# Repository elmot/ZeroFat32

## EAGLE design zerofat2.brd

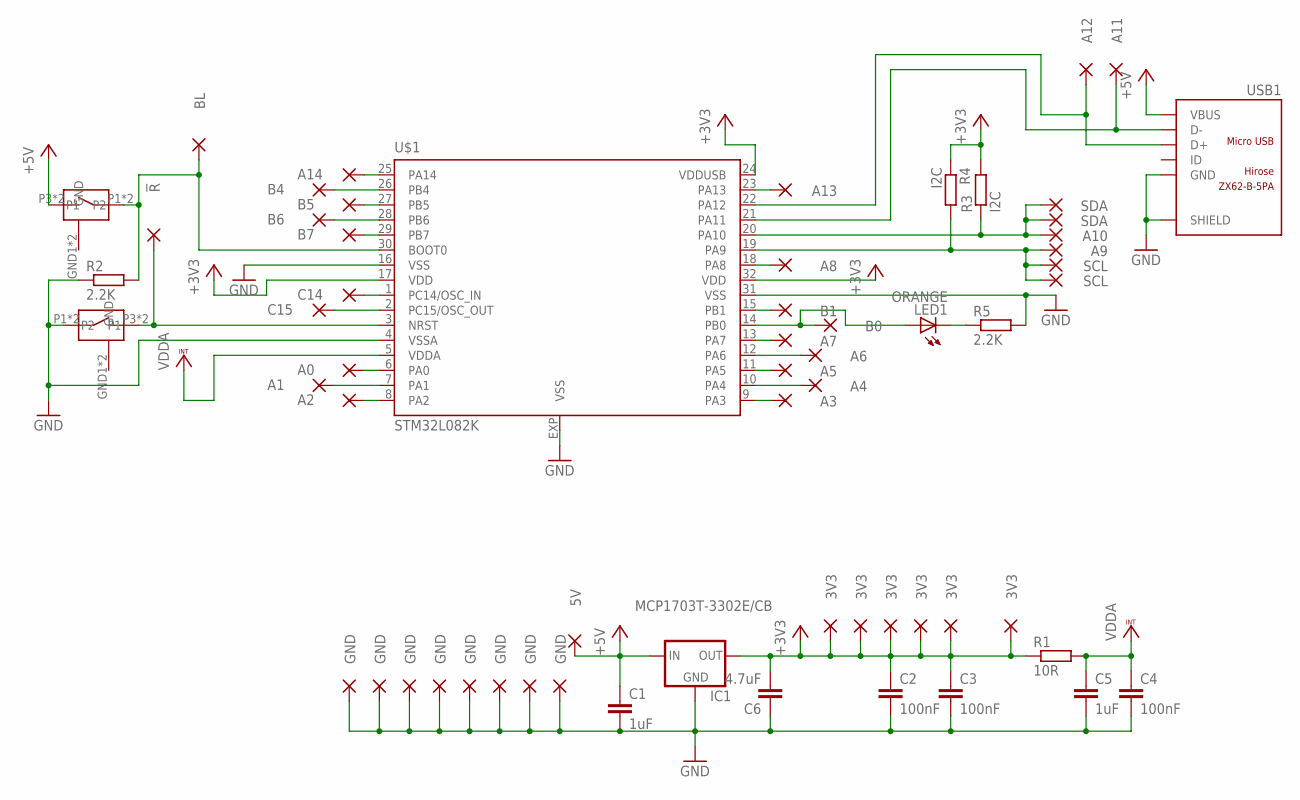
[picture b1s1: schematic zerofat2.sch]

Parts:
B: EVQPT5A15
C1, C5: 1uF; C0603
C2, C3, C4: 100nF; C0603
C6: 4.7uF; C0603
IC1: MCP1703T-3302E/CB; SOT23
LED1: ORANGE; CHIP-LED0603
PAD1, PAD20: SCL; PAD_MINIMAL
PAD2, PAD19: SDA; PAD_MINIMAL
PAD3: C14; PAD_MINIMAL
PAD4: C15; PAD_MINIMAL
PAD5, PAD22, PAD39, PAD43, PAD48, PAD49, PAD50, PAD51: GND; PAD_MINIMAL
PAD6: !R; PAD_MINIMAL
PAD7, PAD15, PAD21, PAD52, PAD53, PAD54: 3V3; PAD_MINIMAL
PAD8: A0; PAD_MINIMAL
PAD9: A2; PAD_MINIMAL
PAD10: A1; PAD_MINIMAL
PAD11: A3; PAD_MINIMAL
PAD12: A5; PAD_MINIMAL
PAD13: A7; PAD_MINIMAL
PAD14: B1; PAD_MINIMAL
PAD16: A4; PAD_MINIMAL
PAD17: A6; PAD_MINIMAL
PAD18: B0; PAD_MINIMAL
PAD24: A8; PAD_MINIMAL
PAD25: A9; PAD_MINIMAL
PAD26: A10; PAD_MINIMAL
PAD27: A13; PAD_MINIMAL
PAD29: A12; PAD_MINIMAL
PAD30: A11; PAD_MINIMAL
PAD31: A14; PAD_MINIMAL
PAD33: B5; PAD_MINIMAL
PAD34: B7; PAD_MINIMAL
PAD35: BL; PAD_MINIMAL
PAD36: B6; PAD_MINIMAL
PAD37: B4; PAD_MINIMAL
PAD45: 5V; PAD_MINIMAL
R: EVQPT5A15
R1: 10R; R0603
R2, R5: 2.2K; R0603
R3, R4: I2C; R0603
U$1: STM32L082K; UFQFPN32
USB1: ZX62-B-5PA; MICRO-USB5+6P-SMD-0.65-AB

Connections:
+3V3: C2.1, C3.1, C6.2, IC1.2 (OUT), PAD7.1, PAD15.1, PAD21.1, PAD52.1, PAD53.1, PAD54.1, R1.1, R3.2, R4.1, U$1.17 (VDD), U$1.24 (VDDUSB), U$1.32 (VDD)
+5V: B.P3 (P2), B.P4 (P2), C1.1, IC1.3 (IN), PAD45.1, USB1.1 (VBUS)
BOOT0: B.P1, B.P2 (P1), PAD35.1, R2.2, U$1.30 (BOOT0)
GND: C1.2, C2.2, C3.2, C4.2, C5.2, C6.1, IC1.1 (GND), PAD5.1, PAD22.1, PAD39.1, PAD43.1, PAD48.1, PAD49.1, PAD50.1, PAD51.1, R.P1, R.P2 (P1), R2.1, R5.2, U$1.4 (VSSA), U$1.16 (VSS), U$1.31 (VSS), U$1.EXP (VSS), USB1.5 (GND), USB1.P1 (SHIELD), USB1.P2 (SHIELD), USB1.P3 (SHIELD), USB1.P4 (SHIELD), USB1.P5 (SHIELD), USB1.P6 (SHIELD)
unnamed: PAD30.1, U$1.21 (PA11), USB1.2 (D-)
unnamed: LED1.A, PAD18.1, U$1.14 (PB0)
unnamed: PAD27.1, U$1.23 (PA13)
unnamed: PAD29.1, U$1.22 (PA12), USB1.3 (D+)
unnamed: PAD31.1, U$1.25 (PA14)
unnamed: PAD3.1, U$1.1 (PC14/OSC_IN)
unnamed: PAD37.1, U$1.26 (PB4)
unnamed: PAD33.1, U$1.27 (PB5)
unnamed: PAD36.1, U$1.28 (PB6)
unnamed: PAD4.1, U$1.2 (PC15/OSC_OUT)
unnamed: PAD8.1, U$1.6 (PA0)
unnamed: PAD10.1, U$1.7 (PA1)
unnamed: PAD9.1, U$1.8 (PA2)
unnamed: PAD11.1, U$1.9 (PA3)
unnamed: PAD16.1, U$1.10 (PA4)
unnamed: PAD12.1, U$1.11 (PA5)
unnamed: PAD17.1, U$1.12 (PA6)
unnamed: PAD13.1, U$1.13 (PA7)
unnamed: PAD24.1, U$1.18 (PA8)
unnamed: PAD14.1, U$1.15 (PB1)
unnamed: PAD1.1, PAD20.1, PAD25.1, R4.2, U$1.19 (PA9)
unnamed: PAD34.1, U$1.29 (PB7)
unnamed: PAD2.1, PAD19.1, PAD26.1, R3.1, U$1.20 (PA10)
unnamed: LED1.C, R5.1
unnamed: PAD6.1, R.P3 (P2), R.P4 (P2), U$1.3 (NRST)
VCCINT: C4.1, C5.1, R1.2, U$1.5 (VDDA)

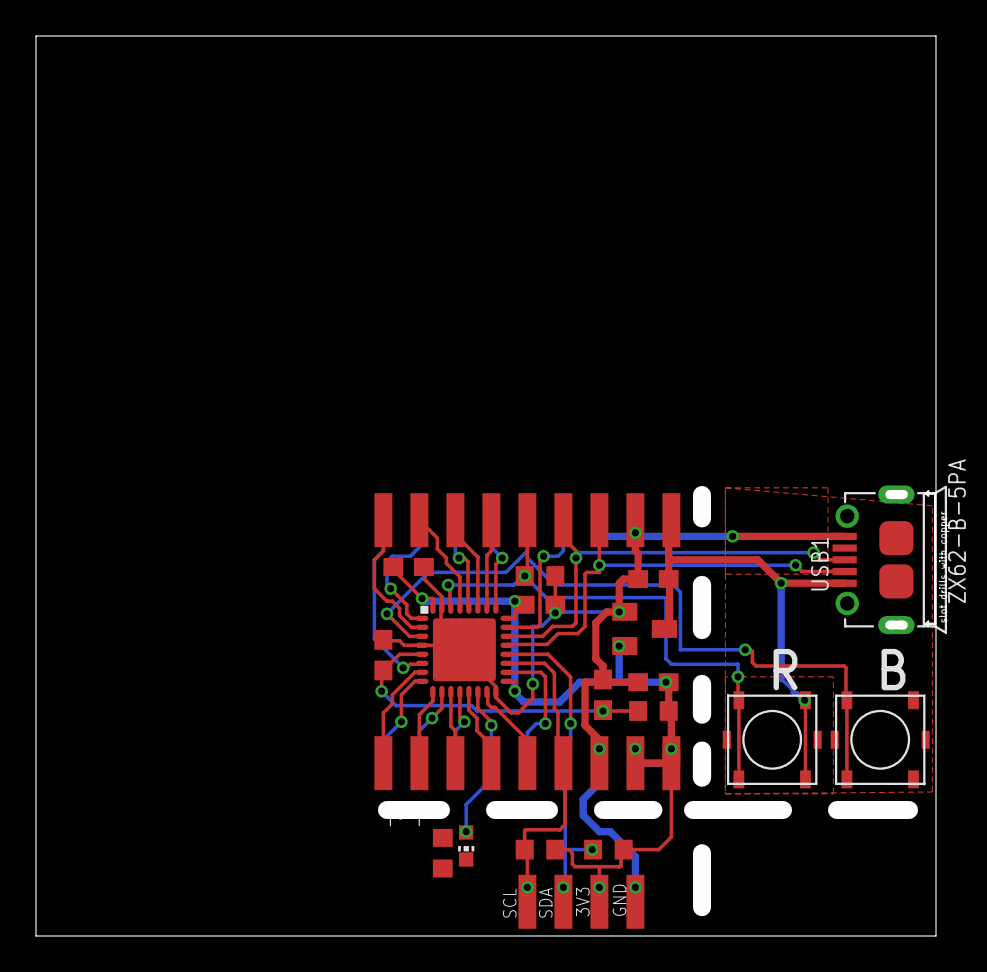
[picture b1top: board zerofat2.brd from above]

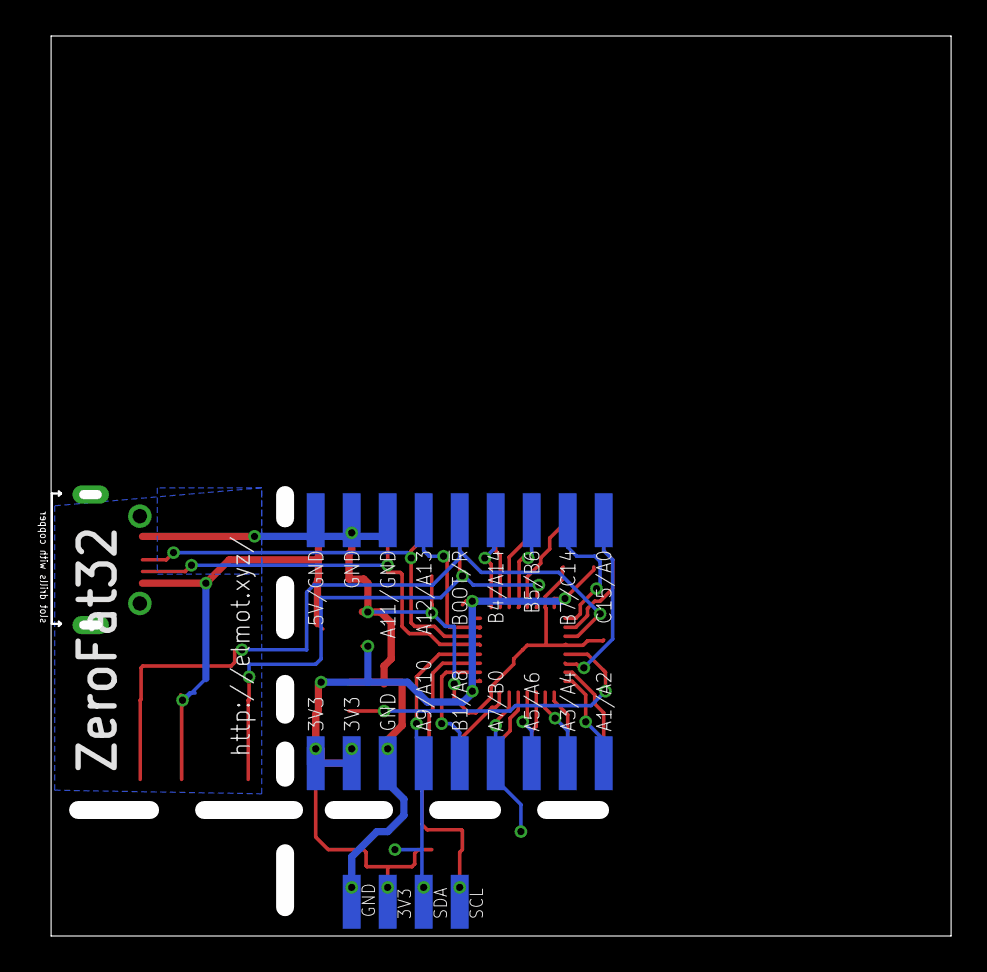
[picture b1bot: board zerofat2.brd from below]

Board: 2 copper layers, 49.8 x 49.0 mm, 61 parts (22 on the bottom side), 30 nets.

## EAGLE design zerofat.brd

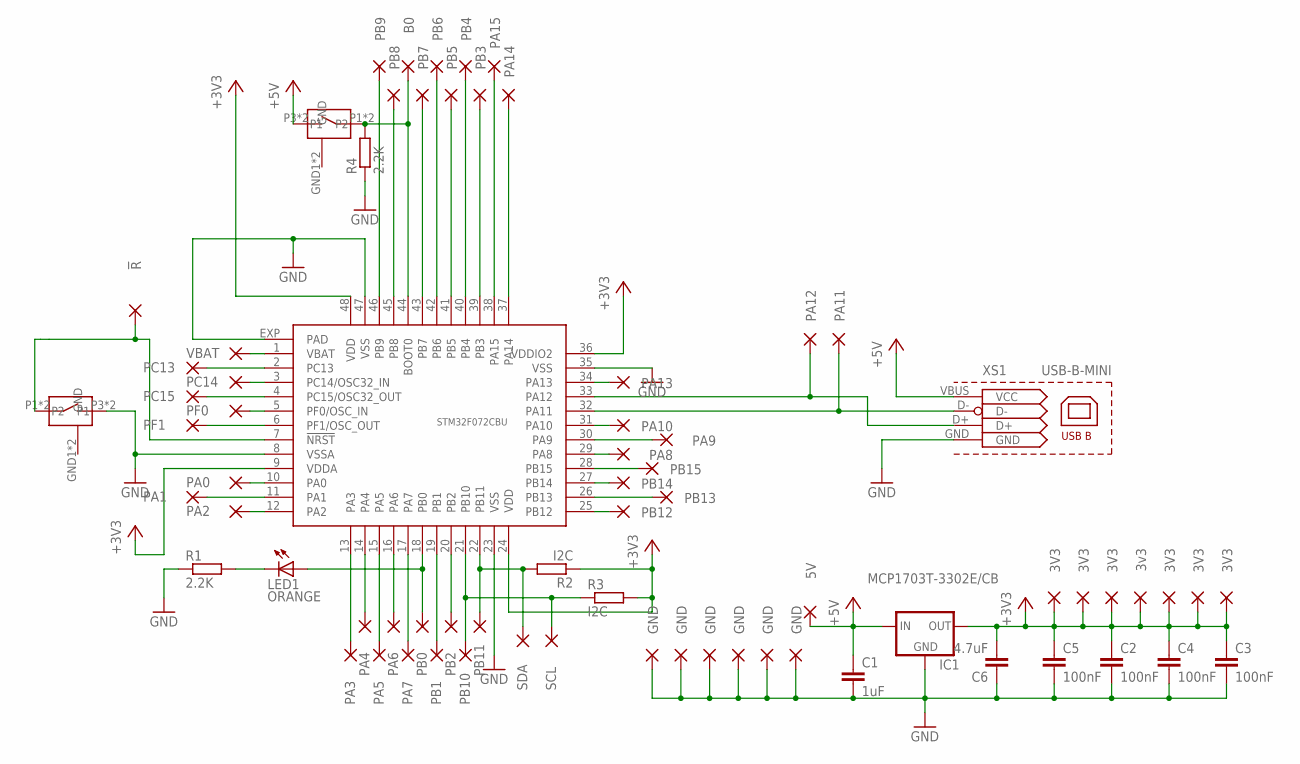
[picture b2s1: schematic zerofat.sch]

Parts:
B: EVQPT5A15
C1: 1uF; C0603K
C2, C3, C4, C5: 100nF; C0603K
C6: 4.7uF; C0603K
IC1: MCP1703T-3302E/CB; SOT23
LED1: ORANGE; CHIP-LED0603
PAD1: VBAT; PAD_MINIMAL
PAD2: PC13; PAD_MINIMAL
PAD3: PC14; PAD_MINIMAL
PAD4: PC15; PAD_MINIMAL
PAD5: PF0; PAD_MINIMAL
PAD6: !R; PAD_MINIMAL
PAD7: PF1; PAD_MINIMAL
PAD8: PA0; PAD_MINIMAL
PAD9: PA2; PAD_MINIMAL
PAD10: PA1; PAD_MINIMAL
PAD11: PA3; PAD_MINIMAL
PAD12: PA5; PAD_MINIMAL
PAD13: PA7; PAD_MINIMAL
PAD14: PB1; PAD_MINIMAL
PAD15: PB10; PAD_MINIMAL
PAD16: PA4; PAD_MINIMAL
PAD17: PA6; PAD_MINIMAL
PAD18: PB0; PAD_MINIMAL
PAD19: PB2; PAD_MINIMAL
PAD20: PB11; PAD_MINIMAL
PAD21: PB12; PAD_MINIMAL
PAD22: PB13; PAD_MINIMAL
PAD23: PB14; PAD_MINIMAL
PAD24: PA8; PAD_MINIMAL
PAD25: PA9; PAD_MINIMAL
PAD26: PA10; PAD_MINIMAL
PAD27: PA13; PAD_MINIMAL
PAD28: PB15; PAD_MINIMAL
PAD29: PA12; PAD_MINIMAL
PAD30: PA11; PAD_MINIMAL
PAD31: PA14; PAD_MINIMAL
PAD32: PB3; PAD_MINIMAL
PAD33: PB5; PAD_MINIMAL
PAD34: PB7; PAD_MINIMAL
PAD35: B0; PAD_MINIMAL
PAD36: PB6; PAD_MINIMAL
PAD37: PB4; PAD_MINIMAL
PAD38: PA15; PAD_MINIMAL
PAD39, PAD46, PAD47, PAD49, PAD50, PAD51: GND; PAD_MINIMAL
PAD40: PB8; PAD_MINIMAL
PAD41: PB9; PAD_MINIMAL
PAD42, PAD44, PAD48, PAD52, PAD53, PAD54: 3V3; PAD_MINIMAL
PAD43: 3v3; PAD_MINIMAL
PAD45: 5V; PAD_MINIMAL
PAD55: SDA; PAD_MINIMAL
PAD56: SCL; PAD_MINIMAL
R: EVQPT5A15
R1, R4: 2.2K; R0603
R2, R3: I2C; R0603
STM32F072CBU: STM32F072CBU; UFQFPN48
XS1: USB-B-MINI; USB-MINIB

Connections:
+3V3: C2.1, C3.1, C4.1, C5.1, C6.2, IC1.2 (OUT), PAD42.1, PAD43.1, PAD44.1, PAD48.1, PAD52.1, PAD53.1, PAD54.1, R2.1, R3.2, STM32F072CBU.9 (VDDA), STM32F072CBU.24 (VDD), STM32F072CBU.36 (VDDIO2), STM32F072CBU.48 (VDD)
+5V: B.P3 (P2), B.P4 (P2), C1.1, IC1.3 (IN), PAD45.1, XS1.VBUS (VCC)
GND: C1.2, C2.2, C3.2, C4.2, C5.2, C6.1, IC1.1 (GND), PAD39.1, PAD46.1, PAD47.1, PAD49.1, PAD50.1, PAD51.1, R.P3 (P2), R.P4 (P2), R1.1, R4.1, STM32F072CBU.8 (VSSA), STM32F072CBU.23 (VSS), STM32F072CBU.35 (VSS), STM32F072CBU.47 (VSS), STM32F072CBU.EXP (PAD), XS1.GND
unnamed: PAD29.1, STM32F072CBU.33 (PA12), XS1.D+
unnamed: LED1.C, R1.2
unnamed: PAD6.1, R.P1, R.P2 (P1), STM32F072CBU.7 (!NRST)
unnamed: PAD30.1, STM32F072CBU.32 (PA11), XS1.D-
unnamed: PAD2.1, STM32F072CBU.2 (PC13)
unnamed: PAD3.1, STM32F072CBU.3 (PC14/OSC32_IN)
unnamed: PAD5.1, STM32F072CBU.5 (PF0/OSC_IN)
unnamed: B.P1, B.P2 (P1), PAD35.1, R4.2, STM32F072CBU.44 (BOOT0)
unnamed: PAD7.1, STM32F072CBU.6 (PF1/OSC_OUT)
unnamed: PAD4.1, STM32F072CBU.4 (PC15/OSC32_OUT)
unnamed: PAD8.1, STM32F072CBU.10 (PA0)
unnamed: PAD9.1, STM32F072CBU.12 (PA2)
unnamed: PAD10.1, STM32F072CBU.11 (PA1)
unnamed: PAD11.1, STM32F072CBU.13 (PA3)
unnamed: PAD16.1, STM32F072CBU.14 (PA4)
unnamed: PAD12.1, STM32F072CBU.15 (PA5)
unnamed: PAD17.1, STM32F072CBU.16 (PA6)
unnamed: PAD13.1, STM32F072CBU.17 (PA7)
unnamed: LED1.A, PAD18.1, STM32F072CBU.18 (PB0)
unnamed: PAD14.1, STM32F072CBU.19 (PB1)
unnamed: PAD19.1, STM32F072CBU.20 (PB2)
unnamed: PAD15.1, PAD56.1, R3.1, STM32F072CBU.21 (PB10)
unnamed: PAD20.1, PAD55.1, R2.2, STM32F072CBU.22 (PB11)
unnamed: PAD21.1, STM32F072CBU.25 (PB12)
unnamed: PAD22.1, STM32F072CBU.26 (PB13)
unnamed: PAD23.1, STM32F072CBU.27 (PB14)
unnamed: PAD24.1, STM32F072CBU.29 (PA8)
unnamed: PAD25.1, STM32F072CBU.30 (PA9)
unnamed: PAD26.1, STM32F072CBU.31 (PA10)
unnamed: PAD31.1, STM32F072CBU.37 (PA14)
unnamed: PAD38.1, STM32F072CBU.38 (PA15)
unnamed: PAD32.1, STM32F072CBU.39 (PB3)
unnamed: PAD37.1, STM32F072CBU.40 (PB4)
unnamed: PAD33.1, STM32F072CBU.41 (PB5)
unnamed: PAD36.1, STM32F072CBU.42 (PB6)
unnamed: PAD34.1, STM32F072CBU.43 (PB7)
unnamed: PAD40.1, STM32F072CBU.45 (PB8)
unnamed: PAD41.1, STM32F072CBU.46 (PB9)
unnamed: PAD27.1, STM32F072CBU.34 (PA13)
unnamed: PAD28.1, STM32F072CBU.28 (PB15)
VBAT: PAD1.1, STM32F072CBU.1 (VBAT)

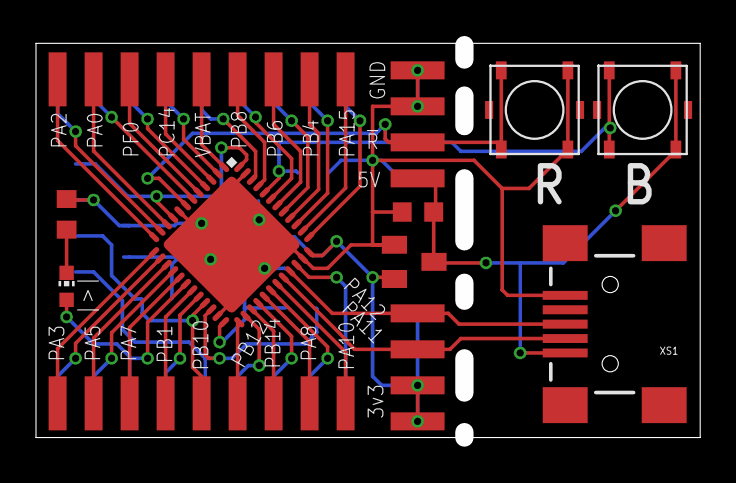
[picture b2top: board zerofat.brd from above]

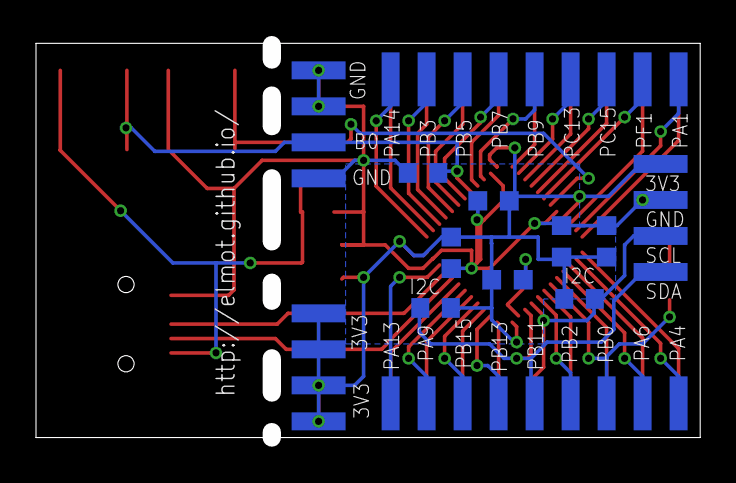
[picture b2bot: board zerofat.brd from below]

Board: 2 copper layers, 35.9 x 21.8 mm, 72 parts (38 on the bottom side), 44 nets.

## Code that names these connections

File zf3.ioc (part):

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Mcu.Name=STM32F072C(8-B)Tx
Mcu.Package=LQFP48
Mcu.UserName=STM32F072CBTx
PA11.Mode=Device
PA11.Signal=USB_DM
PA12.Mode=Device
PA12.Signal=USB_DP
PA13.Mode=Serial-WireDebug
PA13.Signal=SYS_SWDIO
PA14.Mode=Serial-WireDebug
PA14.Signal=SYS_SWCLK
PB0.GPIOParameters=GPIO_ModeDefaultPP,GPIO_Speed,GPIO_PuPd,GPIO_Label
PB0.GPIO_Label=Orange Led
PB0.GPIO_ModeDefaultPP=GPIO_MODE_AF_PP
PB0.GPIO_PuPd=GPIO_NOPULL
PB0.GPIO_Speed=GPIO_SPEED_LOW
PB0.Signal=S_TIM3_CH3
PB10.GPIOParameters=GPIO_Speed,GPIO_PuPdOD,GPIO_Mode
PB10.GPIO_Mode=GPIO_MODE_AF_OD
PB10.GPIO_PuPdOD=GPIO_NOPULL
PB10.GPIO_Speed=GPIO_SPEED_HIGH
PB10.Mode=I2C
PB10.Signal=I2C2_SCL
PB11.GPIOParameters=GPIO_Speed,GPIO_PuPdOD,GPIO_Mode
PB11.GPIO_Mode=GPIO_MODE_AF_OD
PB11.GPIO_PuPdOD=GPIO_NOPULL
PB11.GPIO_Speed=GPIO_SPEED_HIGH
PB11.Mode=I2C
PB11.Signal=I2C2_SDA
RCC.SYSCLKFreq_VALUE=48000000
RCC.SYSCLKSource=RCC_SYSCLKSOURCE_HSI48
board=zf3

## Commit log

2015-09-18 Create gh-pages branch via GitHub
2016-03-13 zerofat2
2016-03-23 ZeroFat32 v2 (STM32L082)
